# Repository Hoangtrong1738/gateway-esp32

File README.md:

# gateway-esp32
ESP32-S3 IoT Gateway board (16MB Flash) featuring W5500 Ethernet, isolated RS-485, and external EEPROM (24LC512). Designed in KiCad (4-layer PCB).

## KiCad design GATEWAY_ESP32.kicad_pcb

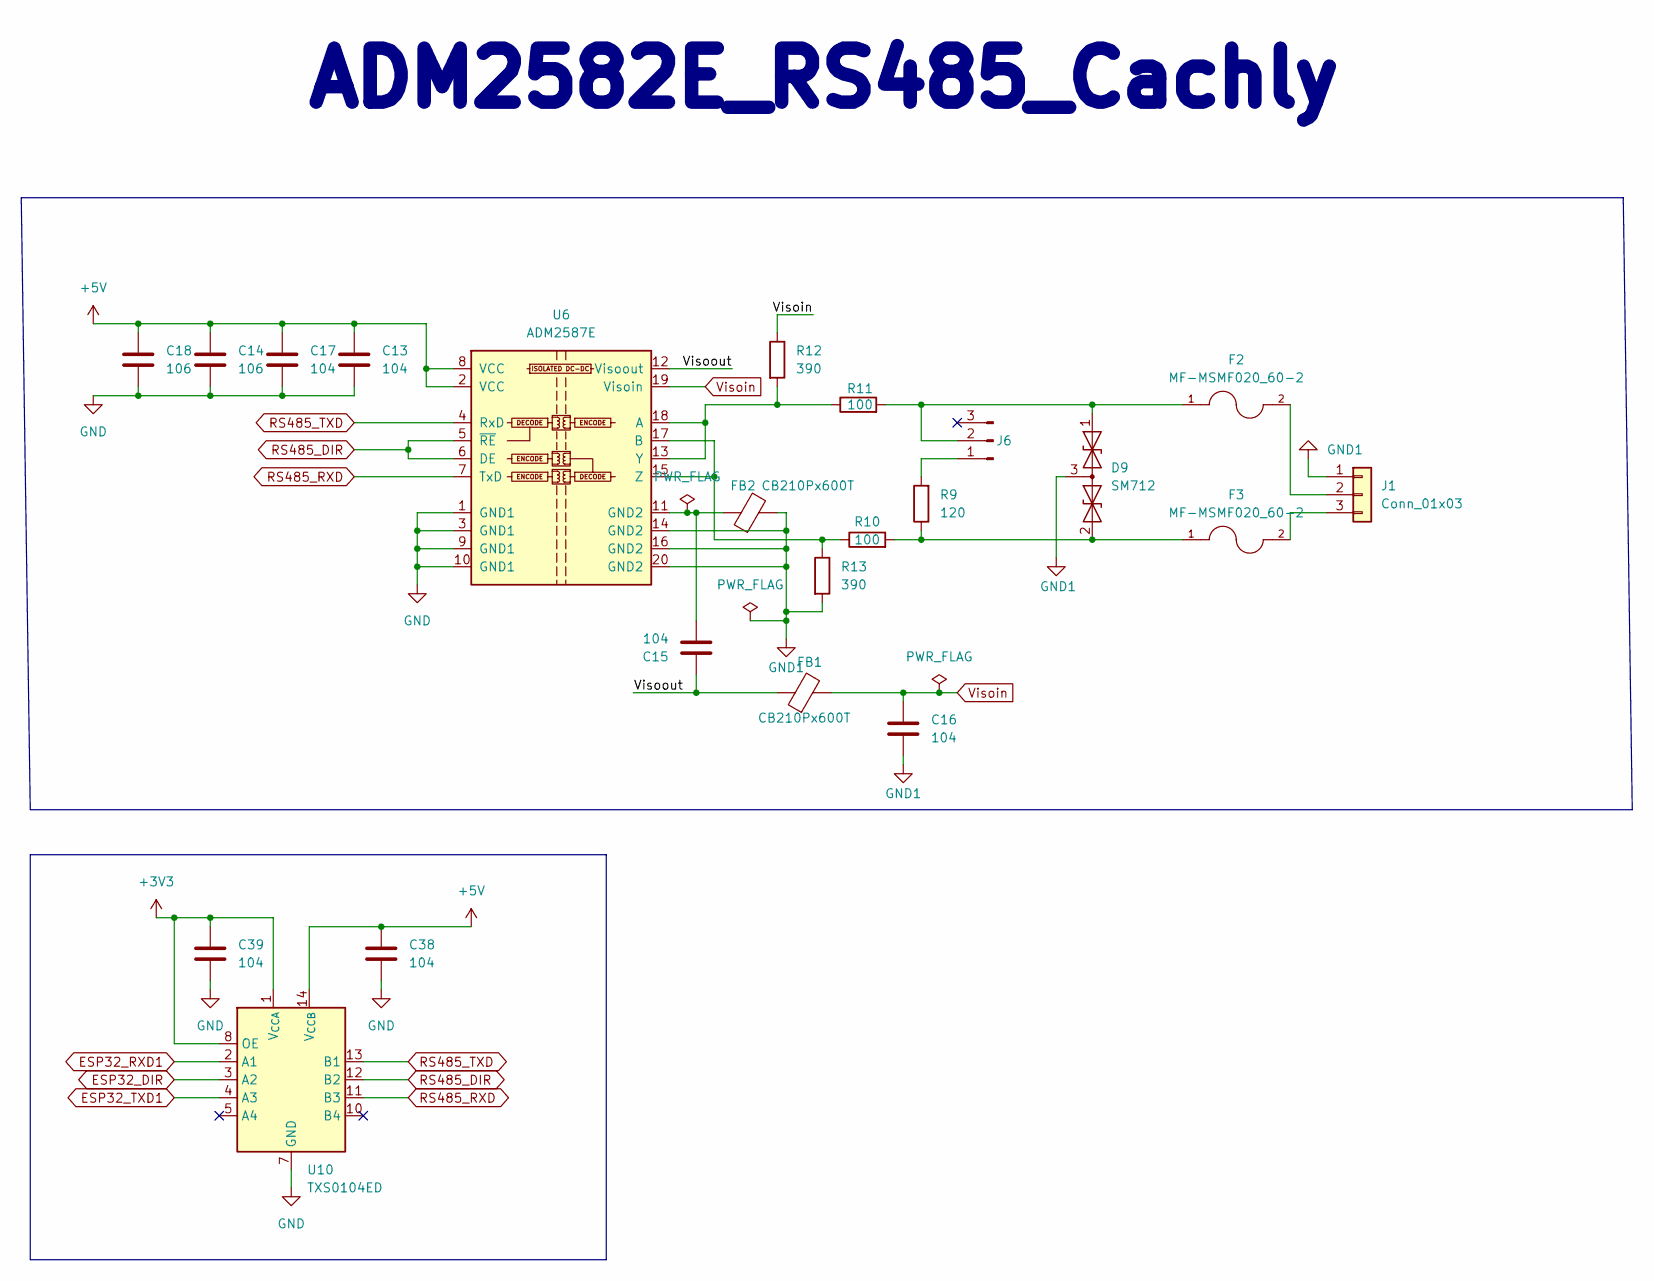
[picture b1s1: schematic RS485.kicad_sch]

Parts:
C13, C15, C16, C17, C38, C39: 104; C_0603_1608Metric
C14, C18: 106; C_0603_1608Metric
D9: SM712; SOT-23
F2, F3: MF-MSMF020_60-2; PTC_1812; MPN MF-MSMF020/60-2
FB1, FB2: CB210Px600T; L_0603_1608Metric
J1: Conn_01x03; PhoenixContact_MSTBA_2,5_3-G-5,08_1x03_P5.08mm_Horizontal
J6: Conn_01x03_Pin; PinHeader_1x03_P2.54mm_Vertical
R9: 120; R_1206_3216Metric
R10, R11: 100; R_1206_3216Metric
R12, R13: 390; R_0603_1608Metric
U6: ADM2587E; SOIC-20W_7.5x12.8mm_P1.27mm
U10: TXS0104ED; SOIC-14_3.9x8.7mm_P1.27mm

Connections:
+3V3: C39.2, U10.1 (V_{CCA}), U10.8 (OE); also elsewhere on the board
+5V: C13.1, C14.1, C17.1, C18.1, C38.2, U6.2 (VCC), U6.8 (VCC), U10.14 (V_{CCB}); also elsewhere on the board
/RS485/Visoout: C15.1, FB1.1, U6.12 (Visoout)
ESP32_DIR: U10.3 (A2); also elsewhere on the board
ESP32_RXD1: U10.2 (A1); also elsewhere on the board
ESP32_TXD1: U10.4 (A3); also elsewhere on the board
GND: C13.2, C14.2, C17.2, C18.2, C38.1, C39.1, U6.1 (GND1), U6.3 (GND1), U6.9 (GND1), U6.10 (GND1), U10.7 (GND); also elsewhere on the board
GND1: C16.2, D9.3 (common), FB2.2, J1.1, R13.2, U6.14 (GND2), U6.16 (GND2), U6.20 (GND2)
unnamed: C15.2, FB2.1, U6.11 (GND2)
unnamed: D9.1 (A1), F2.1, J6.2, R11.2
unnamed: D9.2 (A2), F3.1, R9.1, R10.2
unnamed: F2.2, J1.2
unnamed: F3.2, J1.3
unnamed: J6.1, R9.2
unnamed: R11.1, R12.2, U6.13 (Y), U6.18 (A)
unnamed: R10.1, R13.1, U6.15 (Z), U6.17 (B)
RS485_DIR: U6.5 (~RE), U6.6 (DE), U10.12 (B2)
RS485_RXD: U6.7 (TxD), U10.11 (B3)
RS485_TXD: U6.4 (RxD), U10.13 (B1)
Visoin: C16.1, FB1.2, R12.1, U6.19 (Visoin)

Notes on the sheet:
ADM2582E_RS485_Cachly

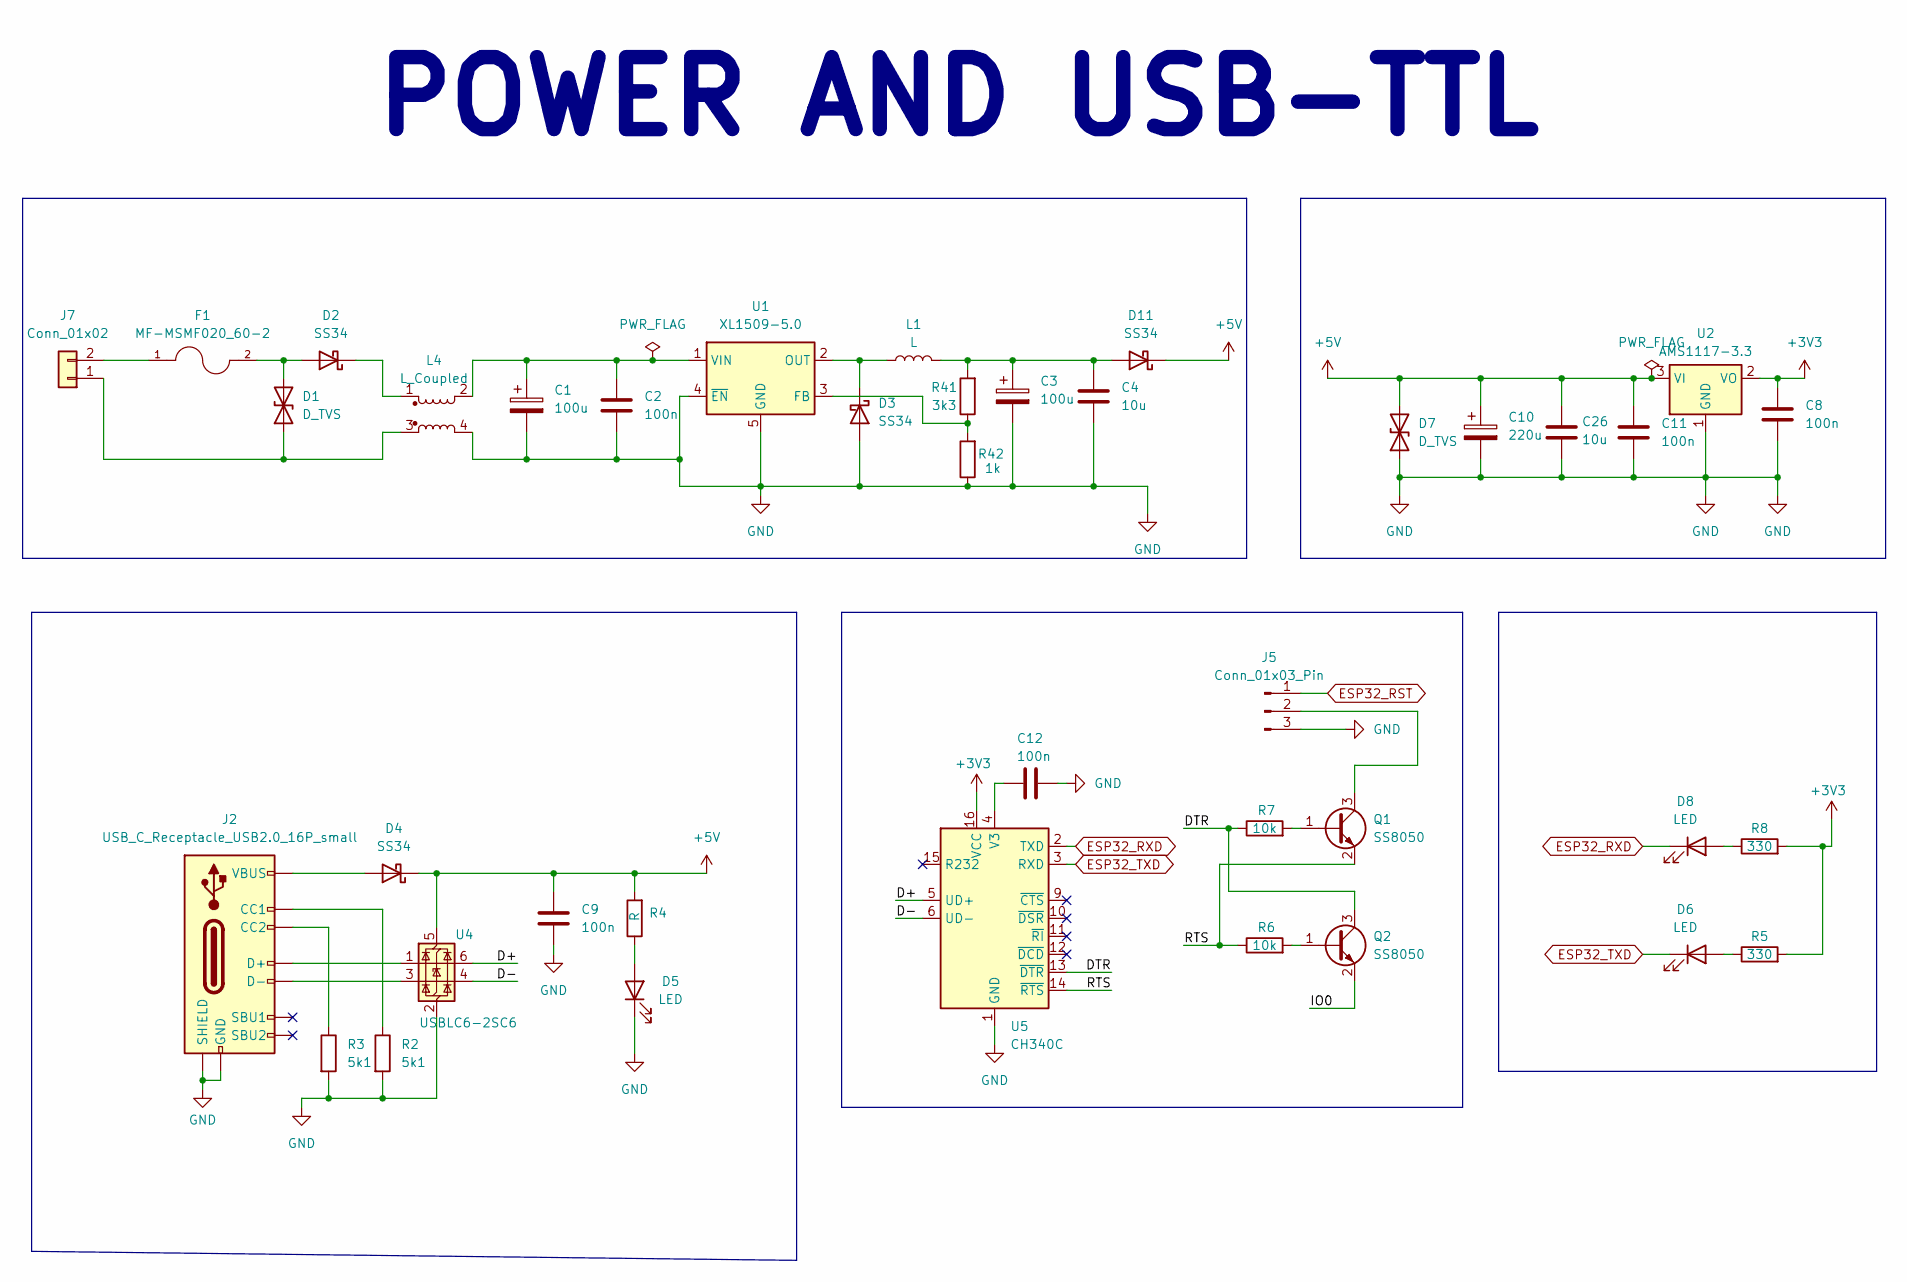
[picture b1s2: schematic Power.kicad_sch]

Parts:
C1, C3: 100u; CP_Elec_10x10.5
C2: 100n; C_0805_2012Metric
C4: 10u; C_1206_3216Metric
C8, C11: 100n; C_1206_3216Metric
C9, C12: 100n; C_0603_1608Metric
C10: 220u; CP_Elec_6.3x7.7
C26: 10u; C_1210_3225Metric
D1, D7: D_TVS; D_SMB_TVS
D2, D3, D4, D11: SS34; D_SMA
D5, D6, D8: LED; LED_0603_1608Metric
F1: MF-MSMF020_60-2; PTC_1812; MPN MF-MSMF020/60-2
J2: USB_C_Receptacle_USB2.0_16P_small; USB-C_12(16)pin_legs
J5: Conn_01x03_Pin; PinHeader_1x03_P2.54mm_Vertical
J7: Conn_01x02; PhoenixContact_MSTBA_2,5_2-G_1x02_P5.00mm_Horizontal
L1: L; L_Bourns_SRP5030T
L4: L_Coupled; L_CommonModeChoke_TDK_ACM7060
Q1, Q2: SS8050; SOT-23
R2, R3: 5k1; R_0603_1608Metric
R4: R; R_0603_1608Metric
R5, R8: 330; R_0603_1608Metric
R6, R7: 10k; R_0603_1608Metric
R41: 3k3; R_0603_1608Metric
R42: 1k; R_0603_1608Metric
U1: XL1509-5.0; SOIC-8_3.9x4.9mm_P1.27mm
U2: AMS1117-3.3; SOT-223-3_TabPin2
U4: USBLC6-2SC6; SOT-23-6
U5: CH340C; SOIC-16_3.9x9.9mm_P1.27mm

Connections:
+3V3: C8.1, R5.2, R8.2, U2.2 (VO), U5.16 (VCC); also elsewhere on the board
+5V: C9.1, C10.1, C11.1, C26.1, D4.1 (K), D7.2 (A2), D11.1 (K), R4.2, U2.3 (VI), U4.5 (VBUS); also elsewhere on the board
/Power and USB TTL/D+: U4.6 (I/O1), U5.5 (UD+)
/Power and USB TTL/D-: U4.4 (I/O2), U5.6 (UD-)
/Power and USB TTL/DTR: Q2.3 (C), R7.1, U5.13 (~DTR)
/Power and USB TTL/IO0: Q2.2 (E)
/Power and USB TTL/RTS: Q1.2 (E), R6.1, U5.14 (~RTS)
ESP32_RST: J5.1; also elsewhere on the board
ESP32_RXD: D8.1 (K), U5.2 (TXD); also elsewhere on the board
ESP32_TXD: D6.1 (K), U5.3 (RXD); also elsewhere on the board
GND: C1.2, C2.2, C3.2, C4.2, C8.2, C9.2, C10.2, C11.2, C12.2, C26.2, D3.2 (A), D5.1 (K), D7.1 (A1), J2.A1 (GND), J2.A12 (GND), J2.B1 (GND), J2.B12 (GND), J2.S1 (SHIELD), J5.3, L4.4, R2.2, R3.2, R42.1, U1.4 (~EN), U1.5 (GND), U1.6 (GND), U1.7 (GND), U1.8 (GND), U2.1 (GND), U4.2 (GND), U5.1 (GND); also elsewhere on the board
unnamed: D1.1 (A1), J7.1, L4.3
unnamed: D1.2 (A2), D2.2 (A), F1.2
unnamed: D2.1 (K), L4.1
unnamed: D3.1 (K), L1.1, U1.2 (OUT)
unnamed: D4.2 (A), J2.A4 (VBUS), J2.A9 (VBUS), J2.B4 (VBUS), J2.B9 (VBUS)
unnamed: D5.2 (A), R4.1
unnamed: D6.2 (A), R5.1
unnamed: D8.2 (A), R8.1
unnamed: C3.1, C4.1, D11.2 (A), L1.2, R41.2
unnamed: J2.A5 (CC1), R2.1
unnamed: J2.B5 (CC2), R3.1
unnamed: J2.A6 (D+), J2.B6 (D+), U4.1 (I/O1)
unnamed: J2.A7 (D-), J2.B7 (D-), U4.3 (I/O2)
unnamed: J5.2, Q1.3 (C)
unnamed: F1.1, J7.2
unnamed: Q1.1 (B), R7.2
unnamed: Q2.1 (B), R6.2
unnamed: R41.1, R42.2, U1.3 (FB)
unnamed: C1.1, C2.1, L4.2, U1.1 (VIN)
unnamed: C12.1, U5.4 (V3)

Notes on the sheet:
POWER AND USB-TTL

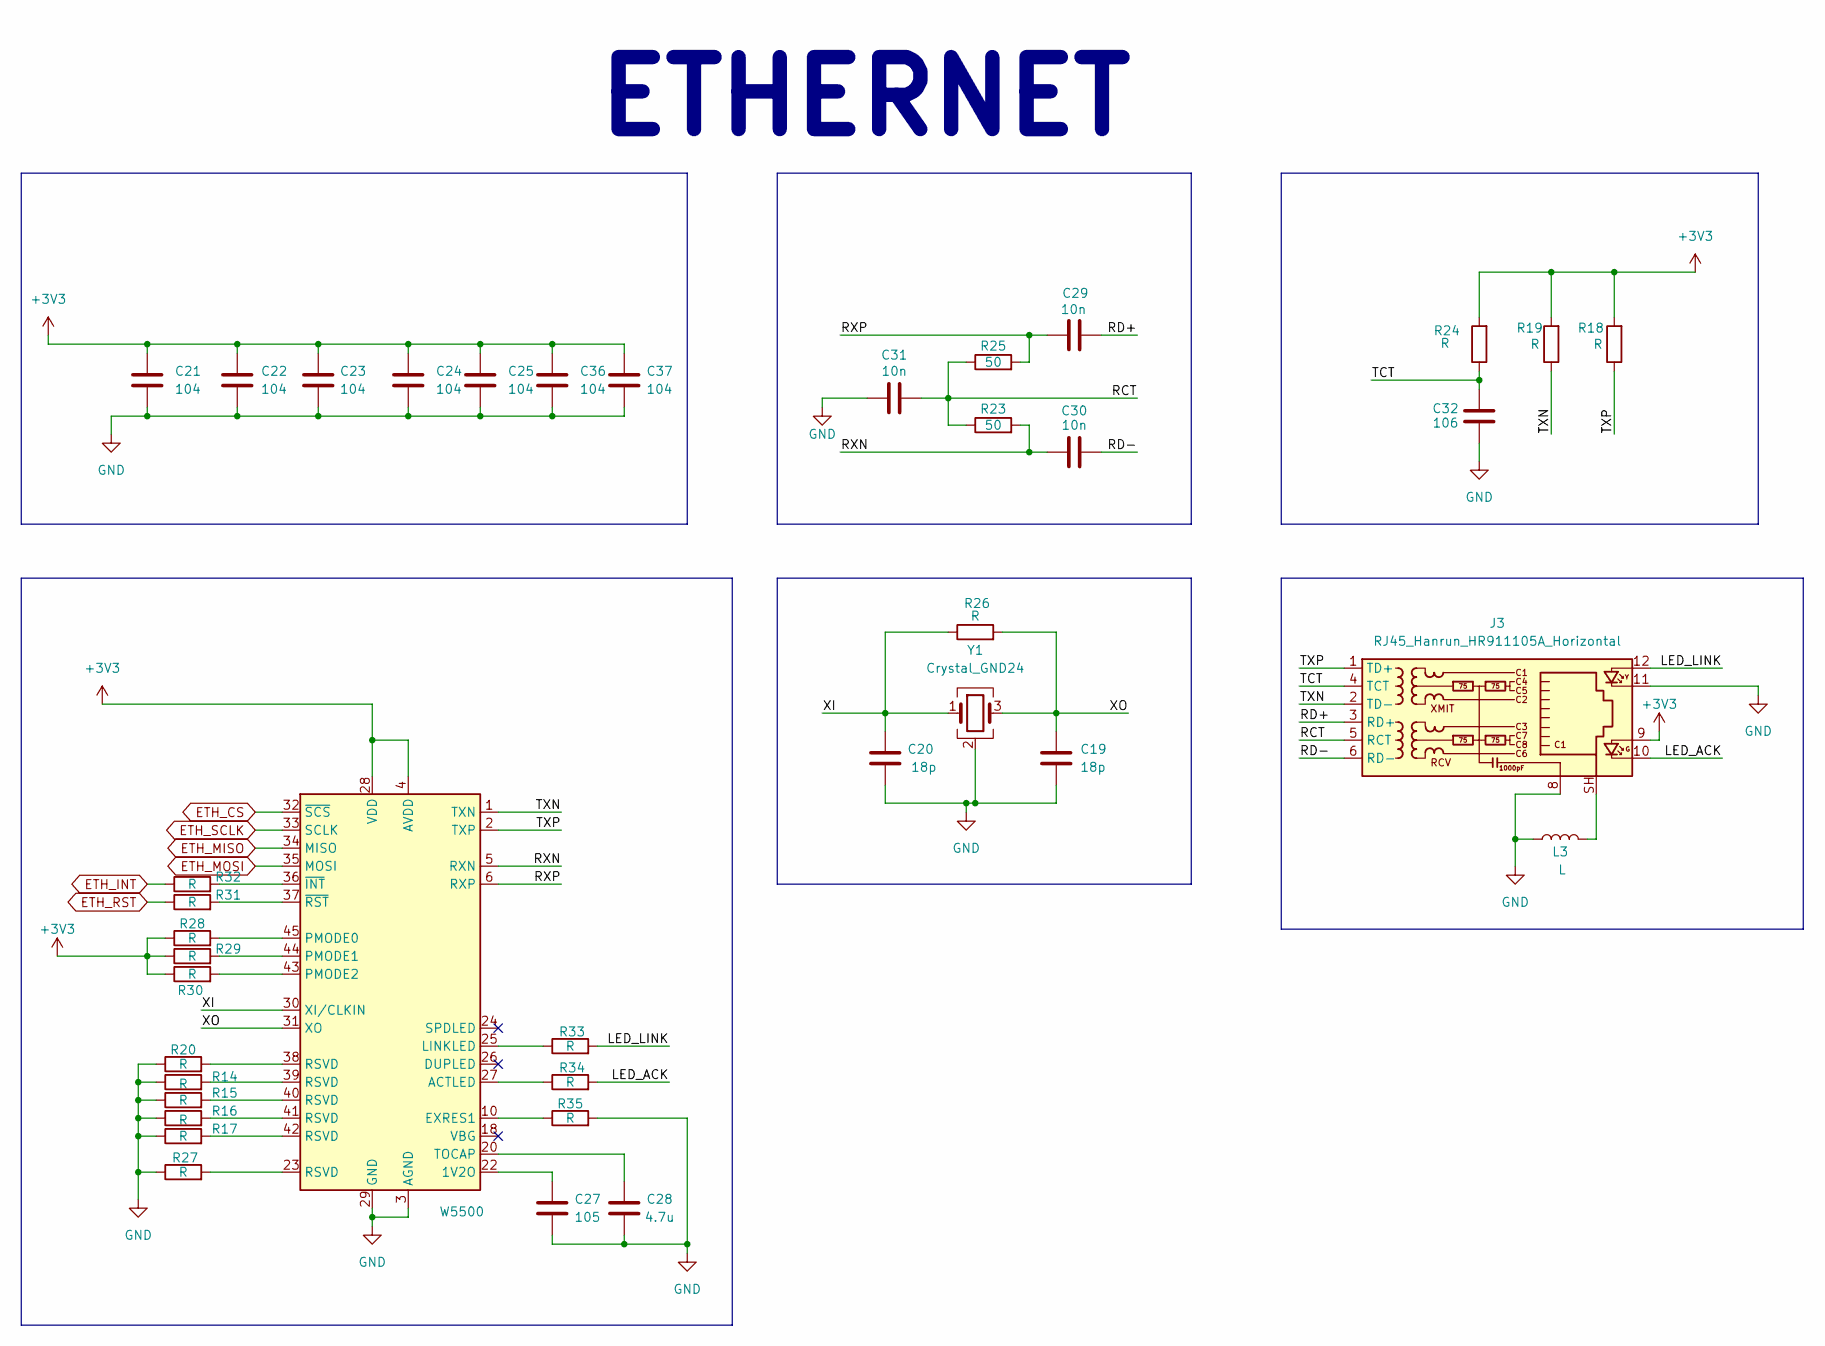
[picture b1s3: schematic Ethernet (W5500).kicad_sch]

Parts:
C19, C20: 18p; C_0603_1608Metric
C21, C22, C23, C24, C25, C36, C37: 104; C_0603_1608Metric
C27: 105; C_0603_1608Metric
C28: 4.7u; C_0603_1608Metric
C29, C30, C31: 10n; C_0603_1608Metric
C32: 106; C_0603_1608Metric
J3: RJ45_Hanrun_HR911105A_Horizontal
L3: L; L_0603_1608Metric
R14, R15, R16, R17, R18, R19, R20, R24, R26, R27, R28, R29, R30, R31, R32, R33, R34, R35: R; R_0603_1608Metric
R23, R25: 50; R_0603_1608Metric
U7: W5500; LQFP-48_7x7mm_P0.5mm
Y1: Crystal_GND24; Crystal_SMD_Abracon_ABM8AIG-4Pin_3.2x2.5mm

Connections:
+3V3: C21.1, C22.1, C23.1, C24.1, C25.1, C36.1, C37.1, J3.9, R18.2, R19.2, R24.2, R28.1, R29.1, R30.1, U7.4 (AVDD), U7.8 (AVDD), U7.11 (AVDD), U7.15 (AVDD), U7.17 (AVDD), U7.21 (AVDD), U7.28 (VDD); also elsewhere on the board
/Ethernet (W5500)/LED_ACK: J3.10, R34.2
/Ethernet (W5500)/LED_LINK: J3.12, R33.2
/Ethernet (W5500)/RCT: C31.2, J3.5 (RCT), R23.1, R25.1
/Ethernet (W5500)/RD+: C29.2, J3.3 (RD+)
/Ethernet (W5500)/RD-: C30.2, J3.6 (RD-)
/Ethernet (W5500)/RXN: C30.1, R23.2, U7.5 (RXN)
/Ethernet (W5500)/RXP: C29.1, R25.2, U7.6 (RXP)
/Ethernet (W5500)/TCT: C32.2, J3.4 (TCT), R24.1
/Ethernet (W5500)/TXN: J3.2 (TD-), R19.1, U7.1 (TXN)
/Ethernet (W5500)/TXP: J3.1 (TD+), R18.1, U7.2 (TXP)
/Ethernet (W5500)/XI: C20.1, R26.1, U7.30 (XI/CLKIN), Y1.1
/Ethernet (W5500)/XO: C19.1, R26.2, U7.31 (XO), Y1.3
ETH_CS: U7.32 (~SCS); also elsewhere on the board
ETH_INT: R32.1; also elsewhere on the board
ETH_MISO: U7.34 (MISO); also elsewhere on the board
ETH_MOSI: U7.35 (MOSI); also elsewhere on the board
ETH_RST: R31.1; also elsewhere on the board
ETH_SCLK: U7.33 (SCLK); also elsewhere on the board
GND: C19.2, C20.2, C21.2, C22.2, C23.2, C24.2, C25.2, C27.2, C28.2, C31.1, C32.1, C36.2, C37.2, J3.8, J3.11, L3.1, R14.1, R15.1, R16.1, R17.1, R20.1, R27.1, R35.2, U7.3 (AGND), U7.9 (AGND), U7.14 (AGND), U7.16 (AGND), U7.19 (AGND), U7.29 (GND), U7.48 (AGND), Y1.2 (G), Y1.4 (G); also elsewhere on the board
unnamed: J3.SH, L3.2
unnamed: R14.2, U7.39 (RSVD)
unnamed: R15.2, U7.40 (RSVD)
unnamed: R16.2, U7.41 (RSVD)
unnamed: R17.2, U7.42 (RSVD)
unnamed: R20.2, U7.38 (RSVD)
unnamed: R27.2, U7.23 (RSVD)
unnamed: C27.1, U7.22 (1V2O)
unnamed: R34.1, U7.27 (ACTLED)
unnamed: R35.1, U7.10 (EXRES1)
unnamed: R33.1, U7.25 (LINKLED)
unnamed: R28.2, U7.45 (PMODE0)
unnamed: R29.2, U7.44 (PMODE1)
unnamed: R30.2, U7.43 (PMODE2)
unnamed: C28.1, U7.20 (TOCAP)
unnamed: R32.2, U7.36 (~INT)
unnamed: R31.2, U7.37 (~RST)

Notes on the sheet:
ETHERNET

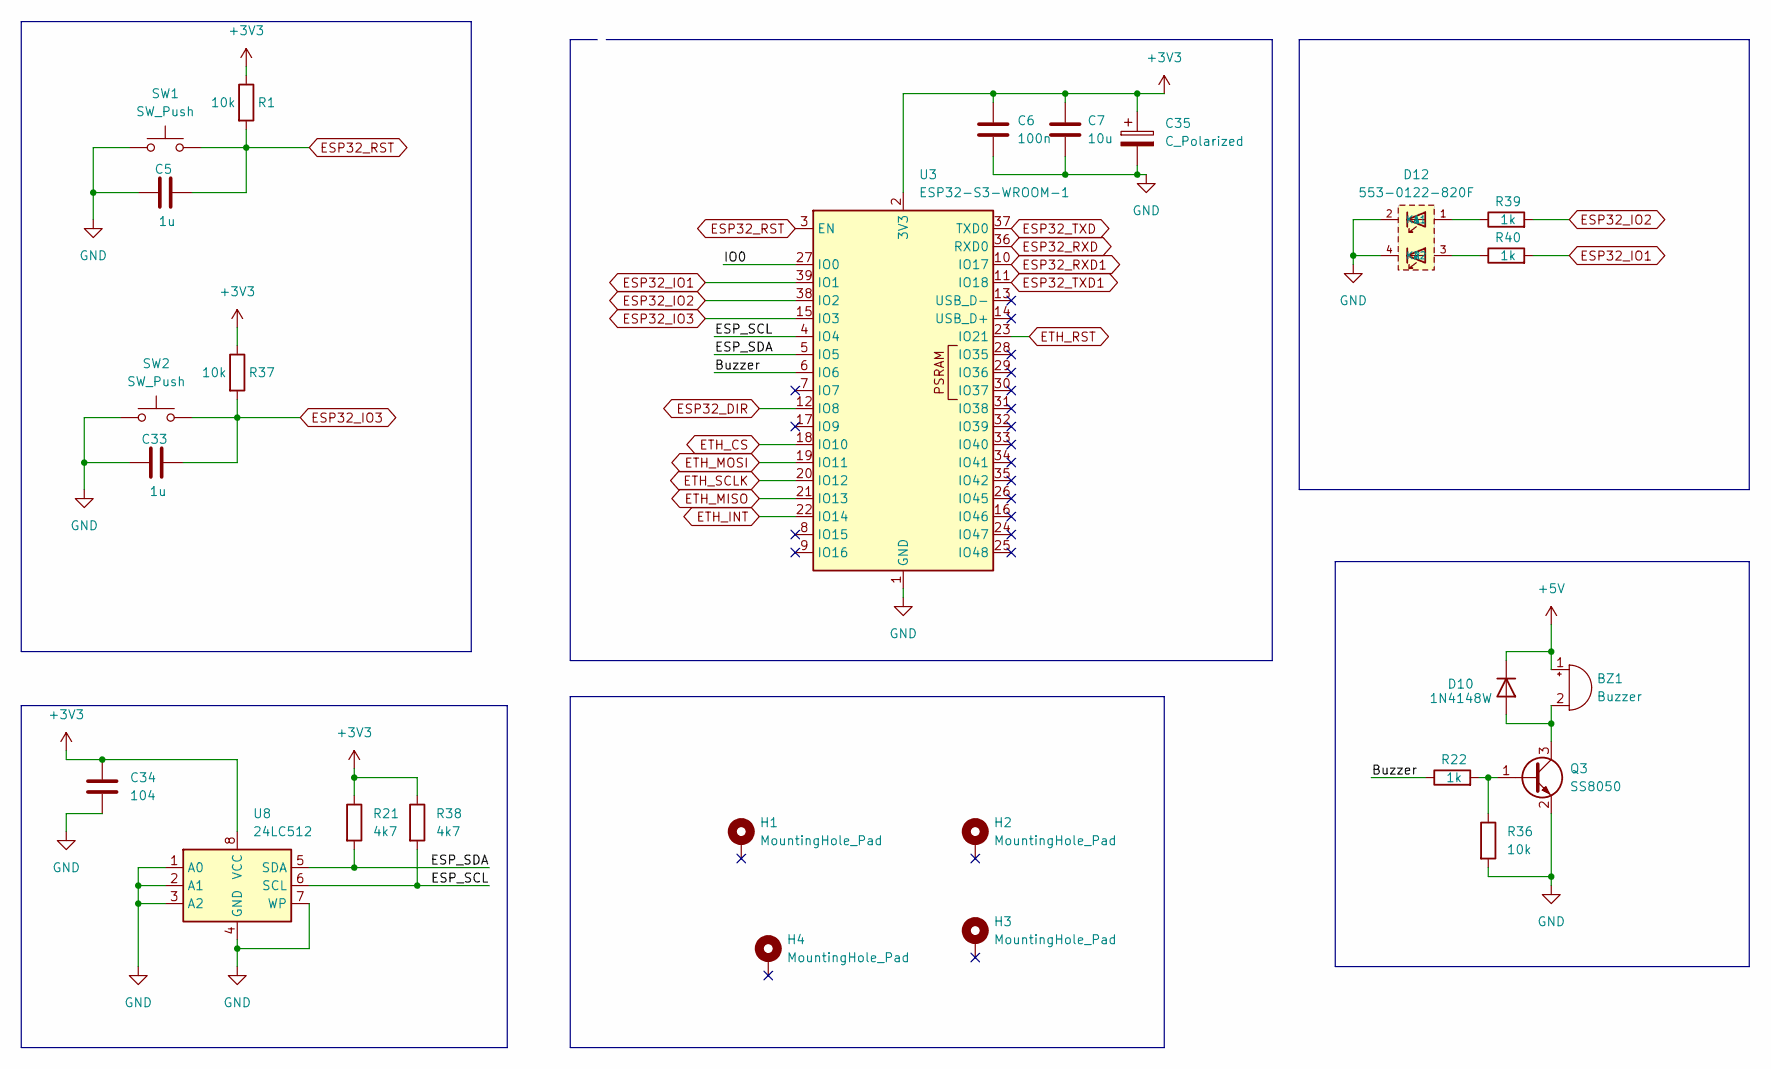
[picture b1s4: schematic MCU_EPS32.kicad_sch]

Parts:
BZ1: Buzzer; Buzzer_12x9.5RM7.6
C5, C33: 1u; C_0603_1608Metric
C6: 100n; C_0603_1608Metric
C7: 10u; C_0603_1608Metric
C34: 104; C_0603_1608Metric
C35: C_Polarized; CP_EIA-3216-18_Kemet-A_HandSolder
D10: 1N4148W; D_SOD-123
D12: 553-0122-820F; Dialight_553-0122-820F
H1, H2, H3, H4: MountingHole_Pad; MountingHole_2.2mm_M2_Pad_Via
Q3: SS8050; SOT-23
R1, R36, R37: 10k; R_0603_1608Metric
R21, R38: 4k7; R_0603_1608Metric
R22, R39, R40: 1k; R_0603_1608Metric
SW1, SW2: SW_Push; SW_Tactile_SPST_NO_Straight_CK_PTS636Sx25SMTRLFS
U3: ESP32-S3-WROOM-1
U8: 24LC512; SOIC-8_3.9x4.9mm_P1.27mm

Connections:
+3V3: C6.1, C7.1, C34.1, C35.1, R1.1, R21.1, R37.1, R38.1, U3.2 (3V3), U8.8 (VCC); also elsewhere on the board
+5V: BZ1.1 (+), D10.1 (K); also elsewhere on the board
/MCU_ESP32/Buzzer: R22.1, U3.6 (IO6)
/MCU_ESP32/ESP_SCL: R38.2, U3.4 (IO4), U8.6 (SCL)
/MCU_ESP32/ESP_SDA: R21.2, U3.5 (IO5), U8.5 (SDA)
/MCU_ESP32/IO0: U3.27 (IO0)
ESP32_DIR: U3.12 (IO8); also elsewhere on the board
ESP32_IO1: R40.2, U3.39 (IO1)
ESP32_IO2: R39.2, U3.38 (IO2)
ESP32_IO3: C33.2, R37.2, SW2.2, U3.15 (IO3)
ESP32_RST: C5.2, R1.2, SW1.2, U3.3 (EN); also elsewhere on the board
ESP32_RXD: U3.36 (RXD0); also elsewhere on the board
ESP32_RXD1: U3.10 (IO17); also elsewhere on the board
ESP32_TXD: U3.37 (TXD0); also elsewhere on the board
ESP32_TXD1: U3.11 (IO18); also elsewhere on the board
ETH_CS: U3.18 (IO10); also elsewhere on the board
ETH_INT: U3.22 (IO14); also elsewhere on the board
ETH_MISO: U3.21 (IO13); also elsewhere on the board
ETH_MOSI: U3.19 (IO11); also elsewhere on the board
ETH_RST: U3.23 (IO21); also elsewhere on the board
ETH_SCLK: U3.20 (IO12); also elsewhere on the board
GND: C5.1, C6.2, C7.2, C33.1, C34.2, C35.2, D12.2 (K1), D12.4 (K2), Q3.2 (E), R36.2, SW1.1, SW2.1, U3.1 (GND), U3.40 (GND), U3.41 (GND), U8.1 (A0), U8.2 (A1), U8.3 (A2), U8.4 (GND), U8.7 (WP); also elsewhere on the board
unnamed: BZ1.2 (-), D10.2 (A), Q3.3 (C)
unnamed: D12.1 (A1), R39.1
unnamed: D12.3 (A2), R40.1
unnamed: Q3.1 (B), R22.2, R36.1

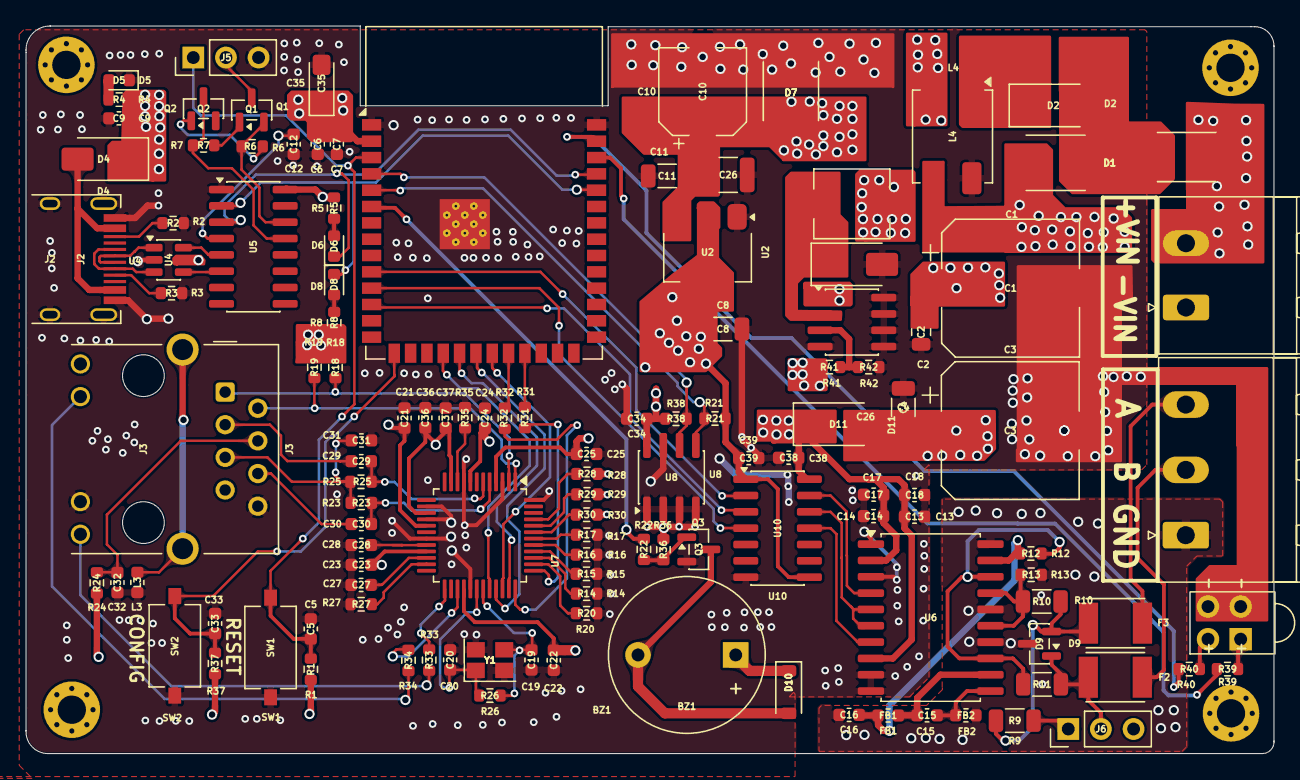
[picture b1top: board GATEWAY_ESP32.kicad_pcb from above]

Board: 4 copper layers, 97.1 x 56.6 mm, 127 parts (0 on the bottom side), 92 nets.
